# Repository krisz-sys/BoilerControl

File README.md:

How it works?<br><br>
The ESP8266 runs a web server that displays various data.
The microcontroller turns on the boiler if:

The slider is triggered by the user

The time schedule is active

The user can set the time schedule via the web interface.
The microcontroller reads the value of a DHT11 temperature sensor from port D7 (GPIO13), and the boiler command is handled by port D5 (GPIO14).
The temperature reading is for informational purposes only.

You can access the web server by entering the IP address into your browser: http://192.168.1.223/ . <br>
Additionally, you need to configure the WiFi SSID and password.

You can see the circuit schematic below:

Here is the PCB layout:

<br><br>

You can find the AutoCAD Eagle design files as HeaterController_PCB.

If the web server is live, you should see the following view. The most important elements are the slider, the temperature value, and the time schedule table:
<br>

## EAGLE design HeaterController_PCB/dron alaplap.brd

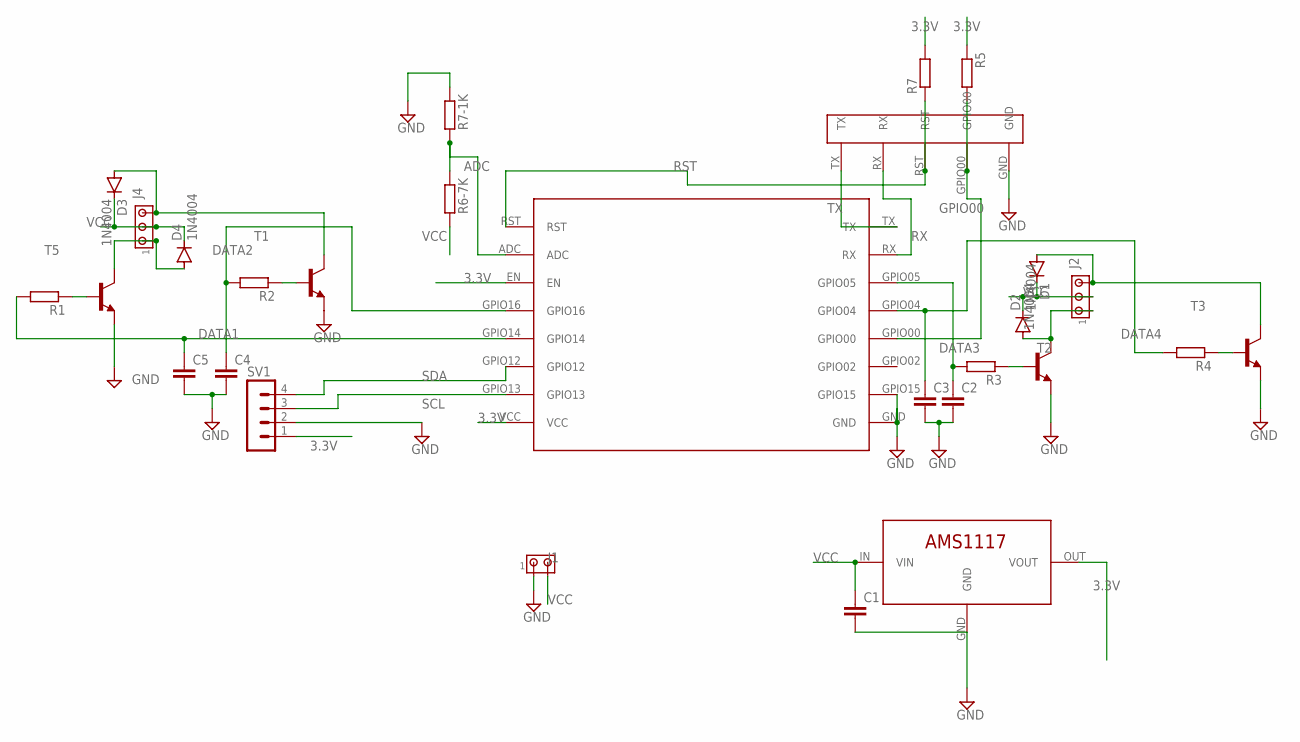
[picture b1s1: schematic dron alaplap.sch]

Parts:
C1: C-EU025-050X050; C025-050X050
C2, C3, C4: C-EU025-030X050; C025-030X050
C5: C-EU050-025X075; C050-025X075
D1, D2, D3, D4: 1N4004; DO41-10
J1: MTA02-156; 1X2MTA
J2, J4: MTA03-156; 1X3MTA
R1, R2, R3, R4, R5, R6-7K, R7-1K: R-EU_0207/12; 0207/12
R7: R-EU_0207/15; 0207/15
SV1: MA04-1
T1, T2, T3, T5: 2N2222-NPN-TO92-EBC; TO92-EBC
U$1: AMS1117
U$2: ESP8266
U$3: PIN

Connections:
3.3V: R5.1, R7.2, SV1.1, U$1.OUT (VOUT), U$2.EN, U$2.VCC
ADC: R6-7K.1, R7-1K.2, U$2.ADC
DATA1: C5.1, R1.2, U$2.GPIO14
DATA2: C4.1, R2.2, U$2.GPIO16
DATA3: C2.1, R3.2, U$2.GPIO05
DATA4: C3.1, R4.2, U$2.GPIO04
GND: C1.2, C2.2, C3.2, C4.2, C5.2, J1.1, R7-1K.1, SV1.2, T1.E, T2.E, T3.E, T5.E, U$1.GND, U$2.GND, U$2.GPIO15, U$3.GND
GPIO00: R5.2, U$2.GPIO00, U$3.GPIO00
unnamed: D4.A, J4.1, T5.C
unnamed: D2.A, J2.1, T2.C
unnamed: R1.1, T5.B
unnamed: D3.A, J4.3, T1.C
unnamed: R2.1, T1.B
unnamed: R3.1, T2.B
unnamed: D1.A, J2.3, T3.C
unnamed: R4.1, T3.B
RST: R7.1, U$2.RST, U$3.RST
RX: U$2.RX, U$3.RX
SCL: SV1.3, U$2.GPIO13
SDA: SV1.4, U$2.GPIO12
TX: U$2.TX, U$3.TX
VCC: C1.1, D1.C, D2.C, D3.C, D4.C, J1.2, J2.2, J4.2, R6-7K.2, U$1.IN (VIN)

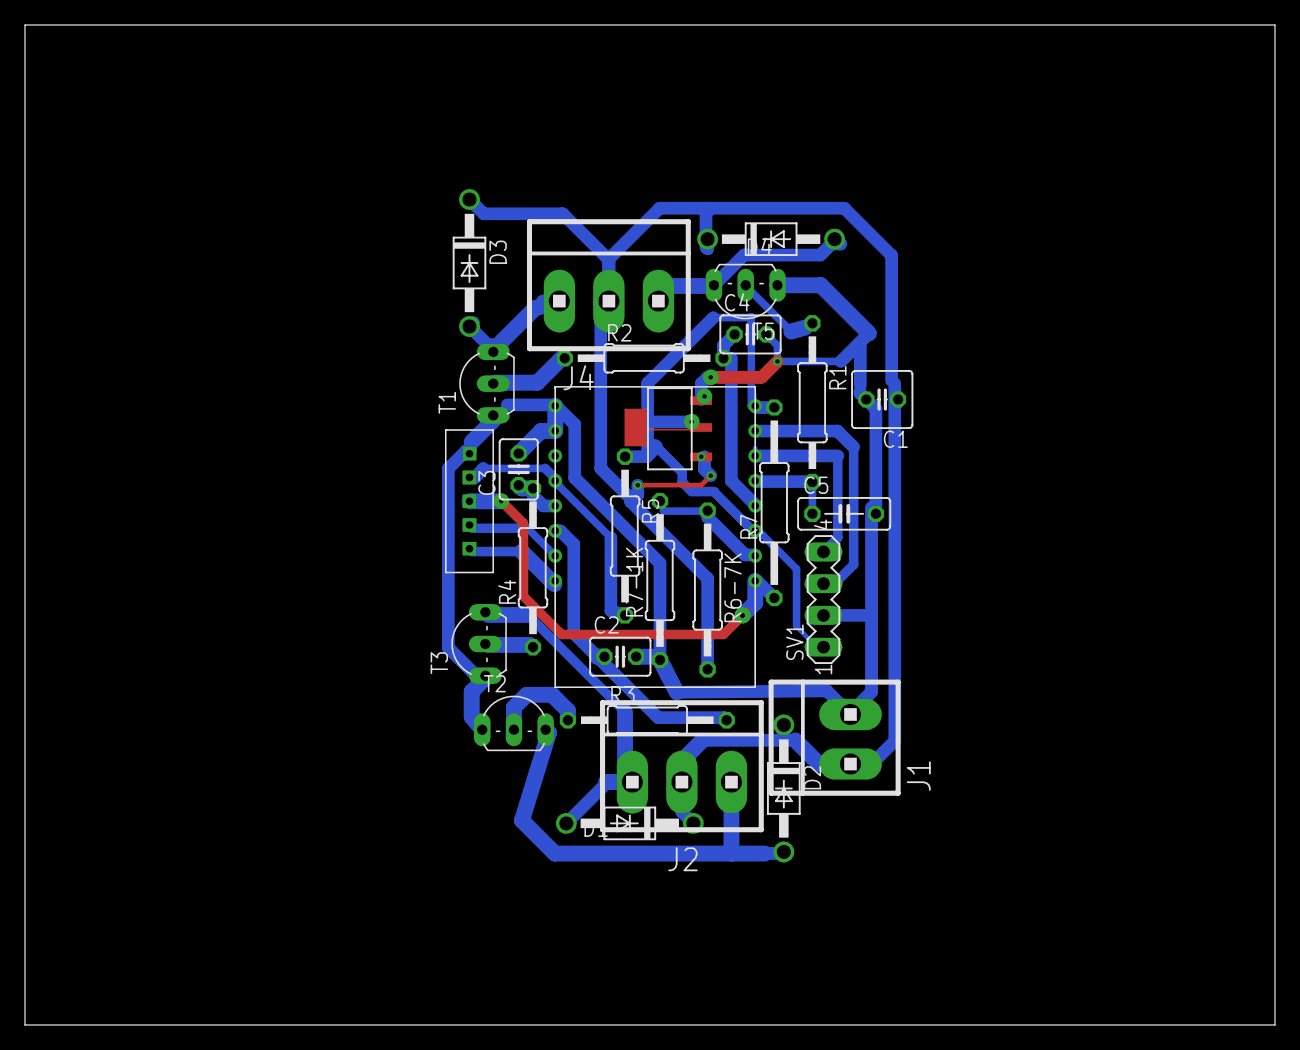
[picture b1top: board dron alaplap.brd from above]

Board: 2 copper layers, 100.0 x 80.0 mm, 28 parts (0 on the bottom side), 22 nets.
